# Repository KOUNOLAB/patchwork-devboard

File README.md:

# Patchwork Playground - dev board

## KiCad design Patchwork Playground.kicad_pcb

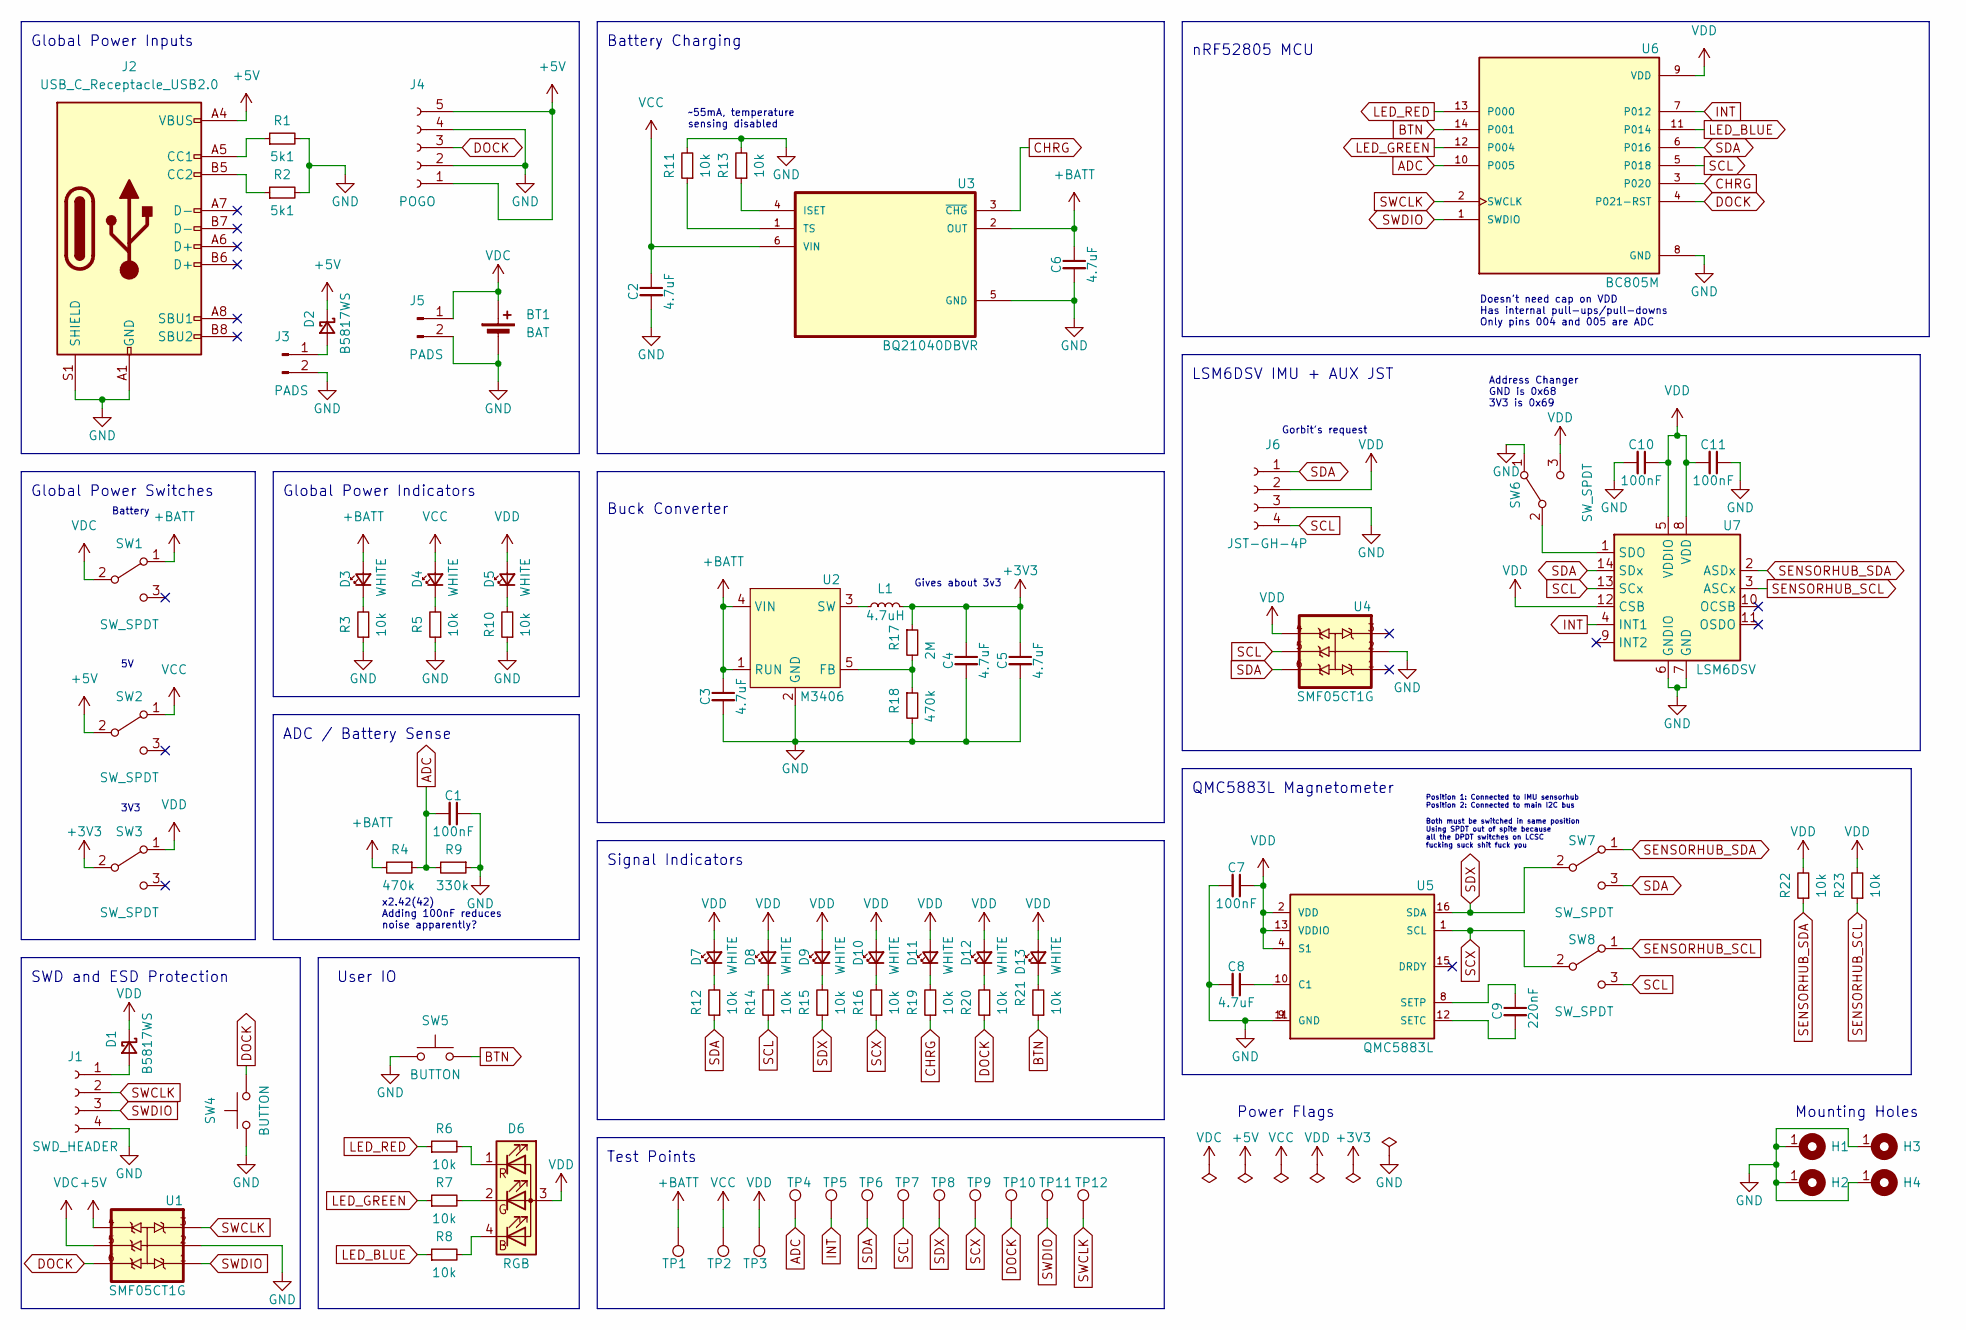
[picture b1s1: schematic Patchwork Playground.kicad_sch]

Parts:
BT1: BAT; JST_PH_S2B-PH-SM4-TB_1x02-1MP_P2.00mm_Horizontal; MPN N/A
C1, C7, C10, C11: 100nF; C_0603_1608Metric; MPN C14663
C2, C3, C4, C5, C6, C8: 4.7uF; C_0603_1608Metric; MPN C19666
C9: 220nF; C_0603_1608Metric; MPN C21120
D1, D2: B5817WS; D_SOD-323; MPN C5178966
D3, D4, D5, D7, D8, D9, D10, D11, D12, D13: WHITE; LED_0603_1608Metric; MPN C2290
D6: RGB; LED_RGB_1210
H1, H2, H3, H4: MountingHole; MountingHole_3.2mm_M3_Pad_Via; MPN N/A
J1: SWD_HEADER; PinHeader_1x04_P2.54mm_Vertical; MPN N/A
J2: USB_C_Receptacle_USB2.0; USB_C_Receptacle_HRO_TYPE-C-31-M-12; MPN C165948
J3, J5: PADS; PinHeader_1x02_P2.54mm_Vertical; MPN N/A
J4: POGO; 5PinPogoFemale; MPN N/A
J6: JST-GH-4P; JST_GH_SM04B-GHS-TB_1x04-1MP_P1.25mm_Horizontal; MPN C189895
L1: 4.7uH; L_0603_1608Metric; MPN C1034
R1, R2: 5k1; R_0603_1608Metric; MPN C23186
R3, R5, R6, R7, R8, R10, R11, R12, R13, R14, R15, R16, R19, R20, R21, R22, R23: 10k; R_0603_1608Metric; MPN C25804
R4, R18: 470k; R_0603_1608Metric; MPN C23178
R9: 330k; R_0603_1608Metric; MPN C23137
R17: 2M; R_0603_1608Metric; MPN C22976
SW1, SW2, SW3, SW6, SW7, SW8: SW_SPDT; MST-22D18G2 3J; MPN C2875122
SW4, SW5: BUTTON; SW_Push_1P1T_XKB_TS-1187A; MPN C318884
TP1, TP2, TP3, TP4, TP5, TP6, TP7, TP8, TP9, TP10, TP11, TP12: TestPoint; TestPoint_Pad_D2.0mm; MPN N/A
U1, U4: SMF05CT1G; SOT65P210X110-6N; MPN C15879
U2: M3406; SOT-23-5; MPN C83224
U3: BQ21040DBVR; SOT-23-6; MPN C202311
U5: QMC5883L; LPCC-16; MPN C976032
U6: BC805M; XCVR_BC805M; MPN C6751361
U7: LSM6DSV; Bosch_LGA-14_3x2.5mm_P0.5mm; MPN C9900037528

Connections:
+3V3: C4.1, C5.1, L1.2, R17.1, SW3.2 (B)
+5V: D2.1 (K), J2.A4 (VBUS), J2.A9 (VBUS), J2.B4 (VBUS), J2.B9 (VBUS), J4.1, J4.5, SW2.2 (B), U1.4
+BATT: C3.1, C6.1, D3.2 (A), R4.2, SW1.1 (A), TP1.1, U2.1 (RUN), U2.4 (VIN), U3.2 (OUT)
ADC: C1.2, R4.1, R9.2, TP4.1, U6.10 (P005)
BTN: R21.1, SW5.2, U6.14 (P001)
CHRG: R19.1, U3.3 (~CHG), U6.3 (P020)
DOCK: J4.3, R20.1, SW4.2, TP10.1, U1.6, U6.4 (P021-RST)
GND: BT1.2 (-), C1.1, C2.2, C3.2, C4.2, C5.2, C6.2, C7.2, C8.2, C10.2, C11.1, H1.1, H2.1, H3.1, H4.1, J1.4, J2.A1 (GND), J2.A12 (GND), J2.B1 (GND), J2.B12 (GND), J2.S1 (SHIELD), J3.2, J4.2, J4.4, J5.2, J6.3, R1.2, R2.2, R3.1, R5.1, R9.1, R10.1, R11.2, R13.2, R18.2, SW4.1, SW5.1, SW6.1 (A), U1.2, U2.2 (GND), U3.5 (GND), U4.2, U5.9 (GND), U5.11 (GND), U6.8 (GND), U7.6 (GNDIO), U7.7 (GND)
INT: TP5.1, U6.7 (P012), U7.4 (INT1)
LED_BLUE: R8.1, U6.11 (P014)
LED_GREEN: R7.1, U6.12 (P004)
LED_RED: R6.1, U6.13 (P000)
unnamed: D1.2 (A), J1.1
unnamed: D2.2 (A), J3.1
unnamed: D3.1 (K), R3.2
unnamed: D4.1 (K), R5.2
unnamed: D5.1 (K), R10.2
unnamed: D6.4 (BK), R8.2
unnamed: D6.2 (GK), R7.2
unnamed: D6.1 (RK), R6.2
unnamed: D7.1 (K), R12.2
unnamed: D8.1 (K), R14.2
unnamed: D9.1 (K), R15.2
unnamed: D10.1 (K), R16.2
unnamed: D11.1 (K), R19.2
unnamed: D12.1 (K), R20.2
unnamed: D13.1 (K), R21.2
unnamed: J2.A5 (CC1), R1.1
unnamed: J2.B5 (CC2), R2.1
unnamed: SW6.2 (B), U7.1 (SDO)
unnamed: R17.2, R18.1, U2.5 (FB)
unnamed: L1.1, U2.3 (SW)
unnamed: R13.1, U3.4 (ISET)
unnamed: R11.1, U3.1 (TS)
unnamed: C8.1, U5.10 (C1)
unnamed: C9.2, U5.12 (SETC)
unnamed: C9.1, U5.8 (SETP)
SCL: J6.4, R14.1, SW8.3 (C), TP7.1, U4.5, U6.5 (P018), U7.13 (SCx)
SCX: R16.1, SW8.2 (B), TP9.1, U5.1 (SCL)
SDA: J6.1, R12.1, SW7.3 (C), TP6.1, U4.6, U6.6 (P016), U7.14 (SDx)
SDX: R15.1, SW7.2 (B), TP8.1, U5.16 (SDA)
SENSORHUB_SCL: R23.1, SW8.1 (A), U7.3 (ASCx)
SENSORHUB_SDA: R22.1, SW7.1 (A), U7.2 (ASDx)
SWCLK: J1.2, TP12.1, U1.3, U6.2 (SWCLK)
SWDIO: J1.3, TP11.1, U1.1, U6.1 (SWDIO)
VCC: C2.1, D4.2 (A), SW2.1 (A), TP2.1, U3.6 (VIN)
VDC: BT1.1 (+), J5.1, SW1.2 (B), U1.5
VDD: C7.1, C10.1, C11.2, D1.1 (K), D5.2 (A), D6.3 (A), D7.2 (A), D8.2 (A), D9.2 (A), D10.2 (A), D11.2 (A), D12.2 (A), D13.2 (A), J6.2, R22.2, R23.2, SW3.1 (A), SW6.3 (C), TP3.1, U4.4, U5.2 (VDD), U5.4 (S1), U5.13 (VDDIO), U6.9 (VDD), U7.5 (VDDIO), U7.8 (VDD), U7.12 (CSB)

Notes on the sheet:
ADC / Battery Sense
Power Flags
Signal Indicators
Gorbit's request
Battery Charging
QMC5883L Magnetometer
x2.42(42) Adding 100nF reduces noise apparently?
Doesn't need cap on VDD Has internal pull-ups/pull-downs Only pins 004 and 005 are ADC
Gives about 3v3
Global Power Indicators
Mounting Holes
Address Changer GND is 0x68 3V3 is 0x69
Buck Converter
3V3
nRF52805 MCU
LSM6DSV IMU + AUX JST
Global Power Inputs
~55mA, temperature sensing disabled
User IO
Global Power Switches
SWD and ESD Protection
Position 1: Connected to IMU sensorhub Position 2: Connected to main I2C bus Both must be switched in same position Using SPDT out of spite because all the DPDT switches on LCSC fucking suck shit fuck you
Test Points
Battery

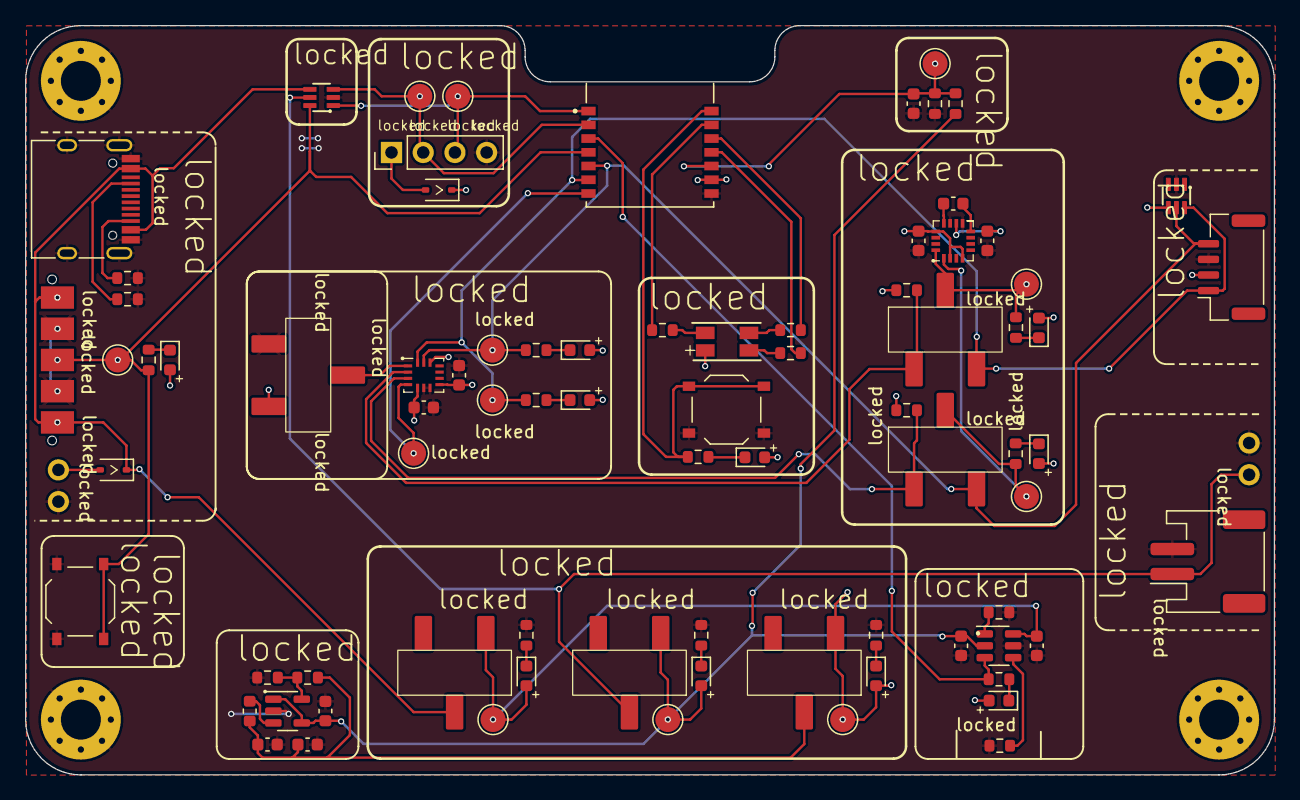
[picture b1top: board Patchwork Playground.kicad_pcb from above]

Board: 2 copper layers, 100.0 x 60.0 mm, 86 parts (0 on the bottom side), 48 nets.

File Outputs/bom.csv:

Designator,Footprint,Quantity,Value,LCSC Part #
"C1, C10, C11, C7",0603,4,100nF,C14663
"C2, C3, C4, C5, C6, C8",0603,6,4.7uF,C19666
C9,0603,1,220nF,C21120
"D1, D2",D_SOD-323,2,B5817WS,C5178966
"D10, D11, D12, D13, D3, D4, D5, D7, D8, D9",0603,10,WHITE,C2290
D6,LED_RGB_1210,1,RGB,
J1,PinHeader_1x04_P2.54mm_Vertical,1,SWD_HEADER,N/A
J2,USB_C_Receptacle_HRO_TYPE-C-31-M-12,1,USB_C_Receptacle_USB2.0,C165948
L1,0603,1,4.7uH,C1034
"R1, R2",0603,2,5k1,C23186
"R10, R11, R12, R13, R14, R15, R16, R19, R20, R21, R22, R23, R3, R5, R6, R7, R8",0603,17,10k,C25804
R17,0603,1,2M,C22976
"R18, R4",0603,2,470k,C23178
R9,0603,1,330k,C23137
"SW1, SW2, SW3, SW6, SW7, SW8",MST-22D18G2 3J,6,SW_SPDT,C2875122
"SW4, SW5",SW_Push_1P1T_XKB_TS-1187A,2,BUTTON,C318884
"U1, U4",SOT65P210X110-6N,2,SMF05CT1G,C15879
U2,SOT-23-5,1,M3406,C83224
U3,SOT-23-6,1,BQ21040DBVR,C202311
U5,LPCC-16,1,QMC5883L,C976032
U6,XCVR_BC805M,1,BC805M,C6751361
U7,Bosch_LGA-14_3x2.5mm_P0.5mm,1,LSM6DSV,C9900037528

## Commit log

2023-11-20 stupid jlc order number
2023-11-20 recenter some silkscreen, replace pogo model
2023-11-20 Bom consolidation UwU
2023-11-20 prettify
2023-11-20 Removed some stuff from BOM owo
2023-11-20 update board img
2023-11-20 change swd footprint
2023-11-23 change adc/buck res values, fix qmc sensorhub pullups
2023-11-23 maybe include the actual prod files you big dummy
2023-11-29 fix fix fix fix fix
2023-11-29 why did it delete gitignore
2023-12-17 v1.1
2023-12-17 Minor routing changes
2023-12-30 Update bom.csv (#1)
